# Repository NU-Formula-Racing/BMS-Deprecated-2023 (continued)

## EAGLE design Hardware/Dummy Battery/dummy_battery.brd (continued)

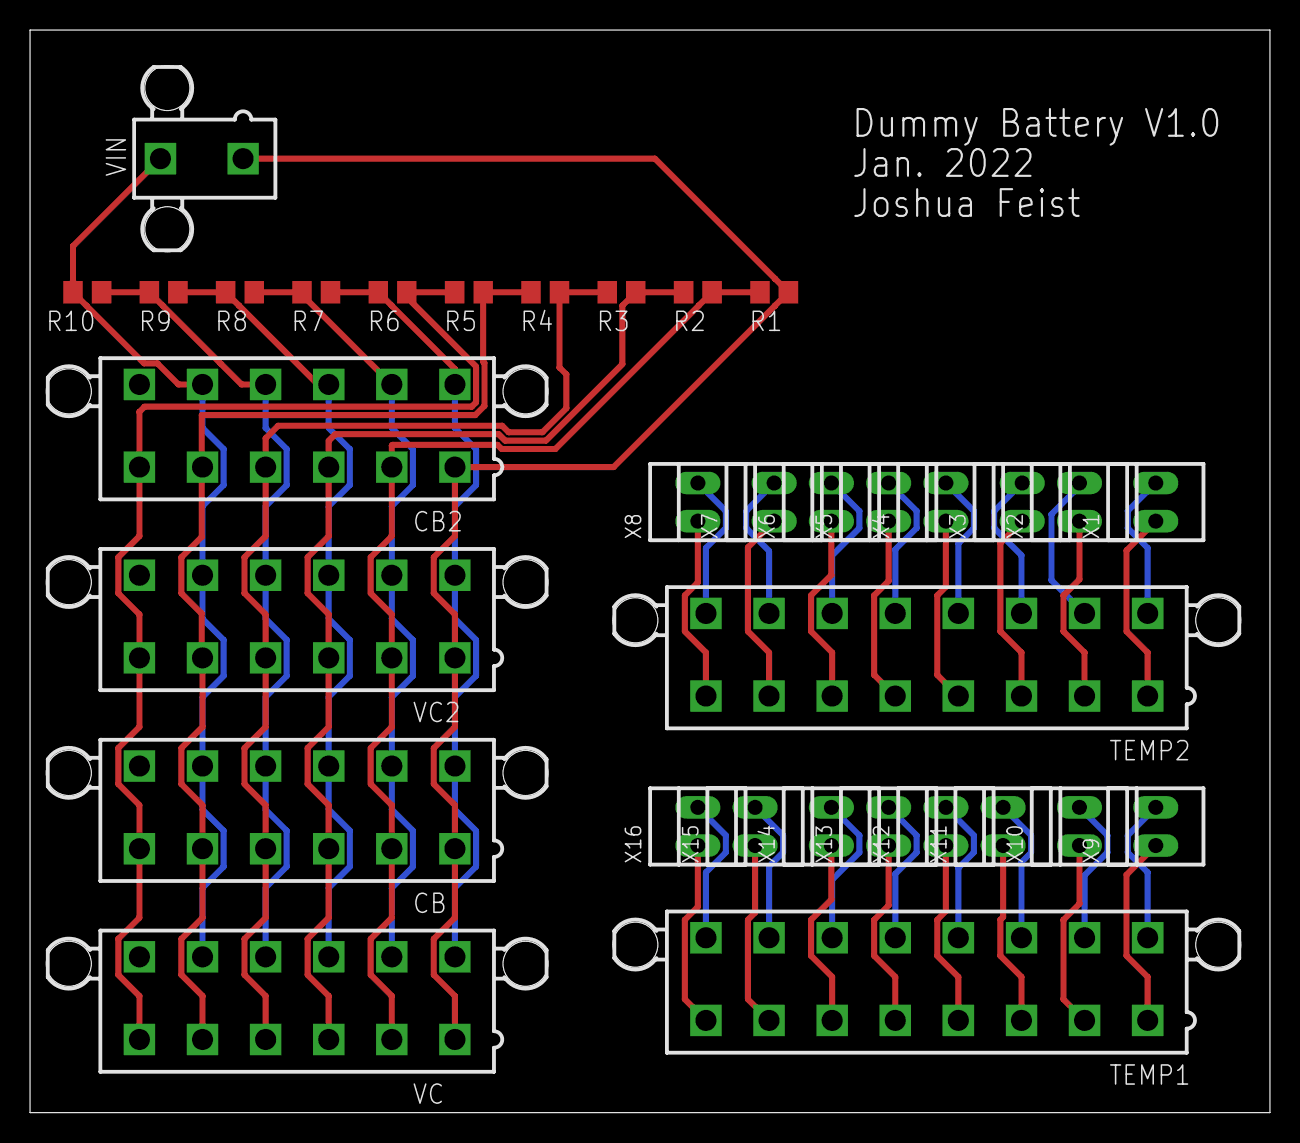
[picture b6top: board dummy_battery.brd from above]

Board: 2 copper layers, 82.5 x 72.1 mm, 33 parts (0 on the bottom side), 43 nets.

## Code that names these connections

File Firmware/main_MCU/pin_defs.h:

#define nfault_pin 16
#define spi_rdy_pin 17
#define coolant_ctrl 20
#define contactorprecharge_ctrl 21
#define contactorp_ctrl 22
#define contactorn_ctrl 23
#define mosi_esp 26
#define sck_esp 27
#define cs_bq 38 //cs0
#define cs_esp 39 //cs1
#define miso_esp 41
#define can_rx 30
#define can_tx 31
#define rx_esp 0
#define tx_esp 1
#define mosi_bq 11
#define miso_bq 12
#define sck_bq 13
#define kill_pins [14, 15, 18, 19, 24, 25, 40, 32, 9, 6, 2, 33]

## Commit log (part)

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2021-10-14 Initial folder config
2021-10-16 Added hex register number definitions
2021-10-19 Added BQ76x6 library
2021-10-23 Arduino library and fixed lbr
2021-10-23 bq79600
2021-10-23 Schematic/eagle
2021-10-28 Modified register definitions with current measuring details from TI
2021-10-31 added a resistor
2021-10-31 teensy and esp32 eagle files
2021-11-07 Connected IC to 10 battery cells
2021-11-08 Replaced batteries with Molex Mini Fit connectors, added values to components, connected unused pins to BAT
2021-11-08 Added units and more components from Figure 10-1
2021-11-09 Added connections to thermistors
2021-11-10 Part of com
2021-11-11 11/10/2021 update of esp schematic
2021-11-13 LDOIN
2021-11-13 Added TVS diode library
2021-11-13 added COMLP and COMLN connection
2021-11-16 Finished daughterboard schematic?
2021-11-16 Fixed second chip, replaced caps with 0603
2021-11-17 Started daughterboard PCB design
2021-11-18 Daughterboard PCB arranging work
2021-11-18 finished main board
2021-11-21 created main board pcb
2021-11-21 edits to board
2021-11-21 Worked on daughterboard PCB
2021-11-22 Worked on daughterboard CB/VC L
2021-11-22 Layout L
2021-11-22 Daughterboard layout
2021-11-22 Worked on routing daughterboard, mostly finished COM
2021-11-22 Connected chip 1 (no ground pours yet)
2021-11-30 Added com isolation to main board
2021-12-01 layout changes to main
2021-12-01 component edit
2021-12-02 fixed some inconsistencies
2021-12-02 recreated pcb
2021-12-02 12/1/2021
2021-12-02 have fun with eagle
2021-12-02 teensy.lbr
2021-12-02 placed some wires
2021-12-02 changed the Teensy chip
2021-12-30 Ground planes on segment
2021-12-30 Board and schematic are consistent, mostly wired, some problems
2021-12-31 Almost done with daughter board
2022-01-02 No more airwires!
2022-01-03 DRC, ERC pass
2022-01-03 Label daughterboard
2022-01-03 Re-ran V1 CAM
2022-01-06 Labeled a couple things in segment schematic
2022-01-08 1/8/2022
2022-01-13 change from uart to spi
2022-01-15 Dummy battery and daughterboard v1.1
2022-01-15 connected some stuff
2022-01-15 Rotated connector to shrink board
2022-01-15 Mainboard routing
2022-01-18 All components on top of daughterboard
2022-01-19 design review changes
2022-01-20 seperate spi
2022-01-20 1/19/2022 changes josh/isaac
2022-01-20 final additions hopefully
2022-01-20 Fixed MOSFETs
2022-01-20 BOMs and CAM
2022-01-20 Ready for order
2022-01-22 Fixed LED issue
2022-01-29 Work on main_mcu
2022-01-29 web server code ESP32
2022-02-17 Added test code (not working yet) for BQ79600
2022-02-20 Fixed LED VCC and resistors, coolant is now PWM, CAN transceiver added, removed unnecessary resistor
2022-02-20 I can talk to the board!
2022-02-22 Work on BQ library, RC fix for SR
2022-02-24 ESP32-devkitc-32D instead ov DEVKIT V1
2022-03-03 tactile switch
2022-03-08 fix holes
2022-03-08 Revert "fix holes"
    This reverts commit f4b1f81d6a6675708ffa55f399a4aff91d83dd67.
2022-03-08 Code and fix holes
2022-04-14 Fixed resistors in layout, moved connectors from edge
2022-04-14 LDOIN test pad
2022-05-09 Schematic progress for mainboard
2022-05-10 level shiffft
2022-05-14 Late night mainboard layout
2022-05-15 Final? V2.0 commit of daughterboard
2022-05-17 dc dc buck converter replace
2022-05-17 buck converter layout
2022-05-17 Daughterboard fixes V2.1
2022-05-25 Mainboard fixes
2022-06-29 PlatformIO UART test code
2022-06-30 bq79656 as submodule
2022-06-30 main_mcu in PlatformIO
2022-06-30 Added . to clang-format
2022-06-30 Added .clang-format
2022-06-30 Made some BQ functions private
2022-08-14 Updated to use library accepting vectors instead of array pointers
2022-08-14 Fetched updated submodule branch name
2022-08-20 updated for bq79656 lib changes
2022-08-20 moved shutdowncar definition
2022-08-21 main_MCU build (#84)
    * updated for bq79656 lib changes
    * moved shutdowncar definition
    * Update Firmware/PlatformIO/main_mcu/src/main_MCU.cpp
2022-09-13 Removed submodule
2022-09-13 Made BMS class, implemented preliminary state machine
2022-09-13 Cleanup
2022-09-13 Added pragma once to bms.h
2022-09-27 Added link to state machine flow chart to README
2022-09-27 Feature/state machine (#85)
    * Removed submodule
    * Made BMS class, implemented preliminary state machine
    * Cleanup
    * Added pragma once to bms.h
    * Added link to state machine flow chart to README
2022-09-27 Added readme
2022-09-27 Added two-color LEDs to BMS daughterboard to indicate balancing current status and direction
2022-10-04 set up fault checking
2022-10-04 specify BMSFault underlying type
2022-10-04 ShutdownCar on fault
2022-10-04 Minor style changes
2022-10-04 Set threshhold values
2022-12-15 NFR Annealer
2023-01-02 Successfully prints cell voltages for one segment
2023-01-02 Reads voltages from one segment in test (#87)
    * Updated to use library accepting vectors instead of array pointers
    * Fetched updated submodule branch name
    * Successfully prints cell voltages for one segment
2023-01-05 Thermistor things
2023-01-05 Added two-color LEDs to BMS daughterboard to indicate balancing current status and direction (#88)
2023-01-08 BMS V3 hardware
2023-01-10 i think sdlogger runs
2023-01-10 V3 done
2023-01-14 Possibly functional SoE calculation (that definitely should be reviewed tho)
2023-01-14 fix dum speelig errror
2023-01-16 Renamed some variables
2023-01-21 Revise undervoltage value
2023-01-21 move minVoltage calculation to process state
2023-01-21 added PR review suggestions
2023-01-21 add thermistor to BMS creation so that project can build
2023-01-21 can bus initialization
2023-01-21 limit power output to 80 kW
2023-01-21 initialize CAN buses
2023-01-22 add thermistor to BMS creation so that project can build (#91)
    * add thermistor to BMS creation so that project can build
    * Delete bms_telemetry.cpp
    * Delete bms_telemetry.h
2023-01-26 fixed max power check in CalculateSOE
2023-01-28 Watchdog initial untested
2023-01-28 Possibly functional SoE calculation (that definitely should be review… (#89)
    * Possibly functional SoE calculation (that definitely should be reviewed tho)
    * fix dum speelig errror
    * Revise undervoltage value
    * move minVoltage calculation to process state
    * added PR review suggestions
    * limit power output to 80 kW
2023-01-31 Renamed a bunch more variables
2023-01-31 Renamed some variables (#90)
    * Renamed some variables
    * Renamed a bunch more variables
2023-01-31 added conditions of changing state to charging and active
2023-01-31 Annealer with captive portal
2023-02-04 initializes voltage/temperature signals and messages
2023-02-11 Instantiated telemetry in BMS
2023-02-11 Tested and working with mainboard V3 and Daughterboard V1.1, stack size 1, to read voltages and current
2023-02-14 pass references to voltages and currents for CAN signals
2023-02-18 updated variable names when initiating BMS Telemetry
2023-02-18 Updated fault reporting when serialdebug
2023-02-22 Added Fault Checking (#86)
    * Added two-color LEDs to BMS daughterboard to indicate balancing current status and direction
    * set up fault checking
    * specify BMSFault underlying type
    * Minor style changes
    * Set threshhold values
    * NFR Annealer
2023-02-23 changes to state transitions before faultcheck was implemented; wip
2023-02-23 Added Fault Checking (#86)
    * Added two-color LEDs to BMS daughterboard to indicate balancing current status and direction
    * set up fault checking
    * specify BMSFault underlying type
    * Minor style changes
    * Set threshhold values
    * NFR Annealer
2023-02-23 trying to implement gwpcharger, wip
2023-02-25 added some current CAN messages
2023-02-28 Test code progress
2023-02-28 Mostly completed BMS telemetry Todo: - Fault Summary Signal - Status BMS State Signal - Status SOC Signal - How to reference BMS enum classes in BMS telemetry when BMS uses BMS telemetry - CAN signal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
2023-02-28 Added some state logic
2023-02-28 Added bms interface for use by telemetry
2023-02-28 Cleaned up main_MCU to use timers, bms.Tick() doesn't need an elapsed time
2023-03-01 Changed signals from being pointers, replaced passed references with getters
2023-03-02 A couple final? things
2023-03-02 Changed signals from being pointers, replaced passed references with … (#95)
    * Changed signals from being pointers, replaced passed references with getters
    * A couple final? things
2023-03-02 BMS inherits publicly from IBMS
2023-03-02 Revert "Changed signals from being pointers, replaced passed references with … (#95)"
    This reverts commit 7d331ace4f03866aea77b0fbd1c84cf1b4e81a91.
2023-03-02 Feature/bms telemetry (#93)
    * add thermistor to BMS creation so that project can build
    * Delete bms_telemetry.cpp
    * Delete bms_telemetry.h
    * can bus initialization
    * initialize CAN buses
    * initializes voltage/temperature signals and messages
2023-03-02 Made some changes from testing with telemetry
2023-03-07 Working with watchdog and telemetry for one segment, some charging things
2023-03-09 State logic (#96)
    * added conditions of changing state to charging and active
    * changes to state transitions before faultcheck was implemented; wip
    * Annealer with captive portal
    * Tested and working with mainboard V3 and Daughterboard V1.1, stack size 1, to read voltages and current
    * Added Fault Checking (#86)
    * Added two-color LEDs to BMS daughterboard to indicate balancing current status and direction
2023-03-30 Preliminary implementation
2023-03-30 added getsoc()
2023-04-01 figuring out problems, if statement mainly
2023-04-01 fixing mistakes, adding current_time difference
2023-04-01 shoud be okay, added elapsed time
2023-04-01 Use main can branch
2023-04-04 decimal id to hex id
2023-04-04 updated more ids
2023-04-16 Sense a voltage and balancing lines
2023-04-18 sense pcb a
2023-04-18 sense pcb b
2023-04-19 Äll sense boards done
2023-04-19 all sense boards done
2023-04-19 fixed outline, updated gerbers
2023-04-20 chargers
2023-04-20 adding elcon
2023-04-21 Sense cable test board
2023-04-25 fixed problem with std::array in checking if ow check is complete
2023-04-27 added
2023-04-27 added open wire check to bms
2023-05-04 sense PCB 3D models
2023-05-14 Switched to eGaN FETs
2023-05-15 Switched to single connector for mainboard, generated gerbers
2023-05-15 Labelled HV/LV on mainboard
2023-05-17 Updates from feedback
2023-06-11 Changes, gerbers
2023-06-13 Mainboard update (#101)
    * Switched to eGaN FETs
    * Switched to single connector for mainboard, generated gerbers
    * Labelled HV/LV on mainboard
    * Updates from feedback
    * Changes, gerbers
2023-06-13 Current code with added charger functionality
2023-06-13 Changed IDs to hex
2023-06-13 Always count coulombs
2023-06-14 Added shutdown circuit sensing
2023-06-14 Removed digitalread of charger pin
2023-06-14 Tested, seems to be working soc
2023-06-14 Feature/state of charge (#97)
    * added getsoc()
    * figuring out problems, if statement mainly
    * fixing mistakes, adding current_time difference
    * shoud be okay, added elapsed time
    * Always count coulombs
    * Tested, seems to be working soc
2023-06-14 OWC passes
2023-06-14 OWC working, changed external kill fault, fixed external kill fault
2023-06-14 Feature/open wire check (#100)
    * added
    * added open wire check to bms
    * OWC passes
    * OWC working, changed external kill fault, fixed external kill fault
    ---------
2023-06-23 high current charging, updates from comp
2023-06-23 Feature/elcon (#99)
    * added getsoc()
    * figuring out problems, if statement mainly
    * fixing mistakes, adding current_time difference
    * shoud be okay, added elapsed time
    * chargers
    * adding elcon
